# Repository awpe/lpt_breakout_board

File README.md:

lpt_breakout_board
==================

IEEE1284 breakout board

This is a KiCad (http://www.kicad-pcb.org/) project.

Device allows to select controller for I/O pins.

contact information:

fb:    https://www.facebook.com/awpe00
vk:    http://vk.com/id2616793
tw:    http://twitter.com/lantcant
gmail: awpe00@gmail.com

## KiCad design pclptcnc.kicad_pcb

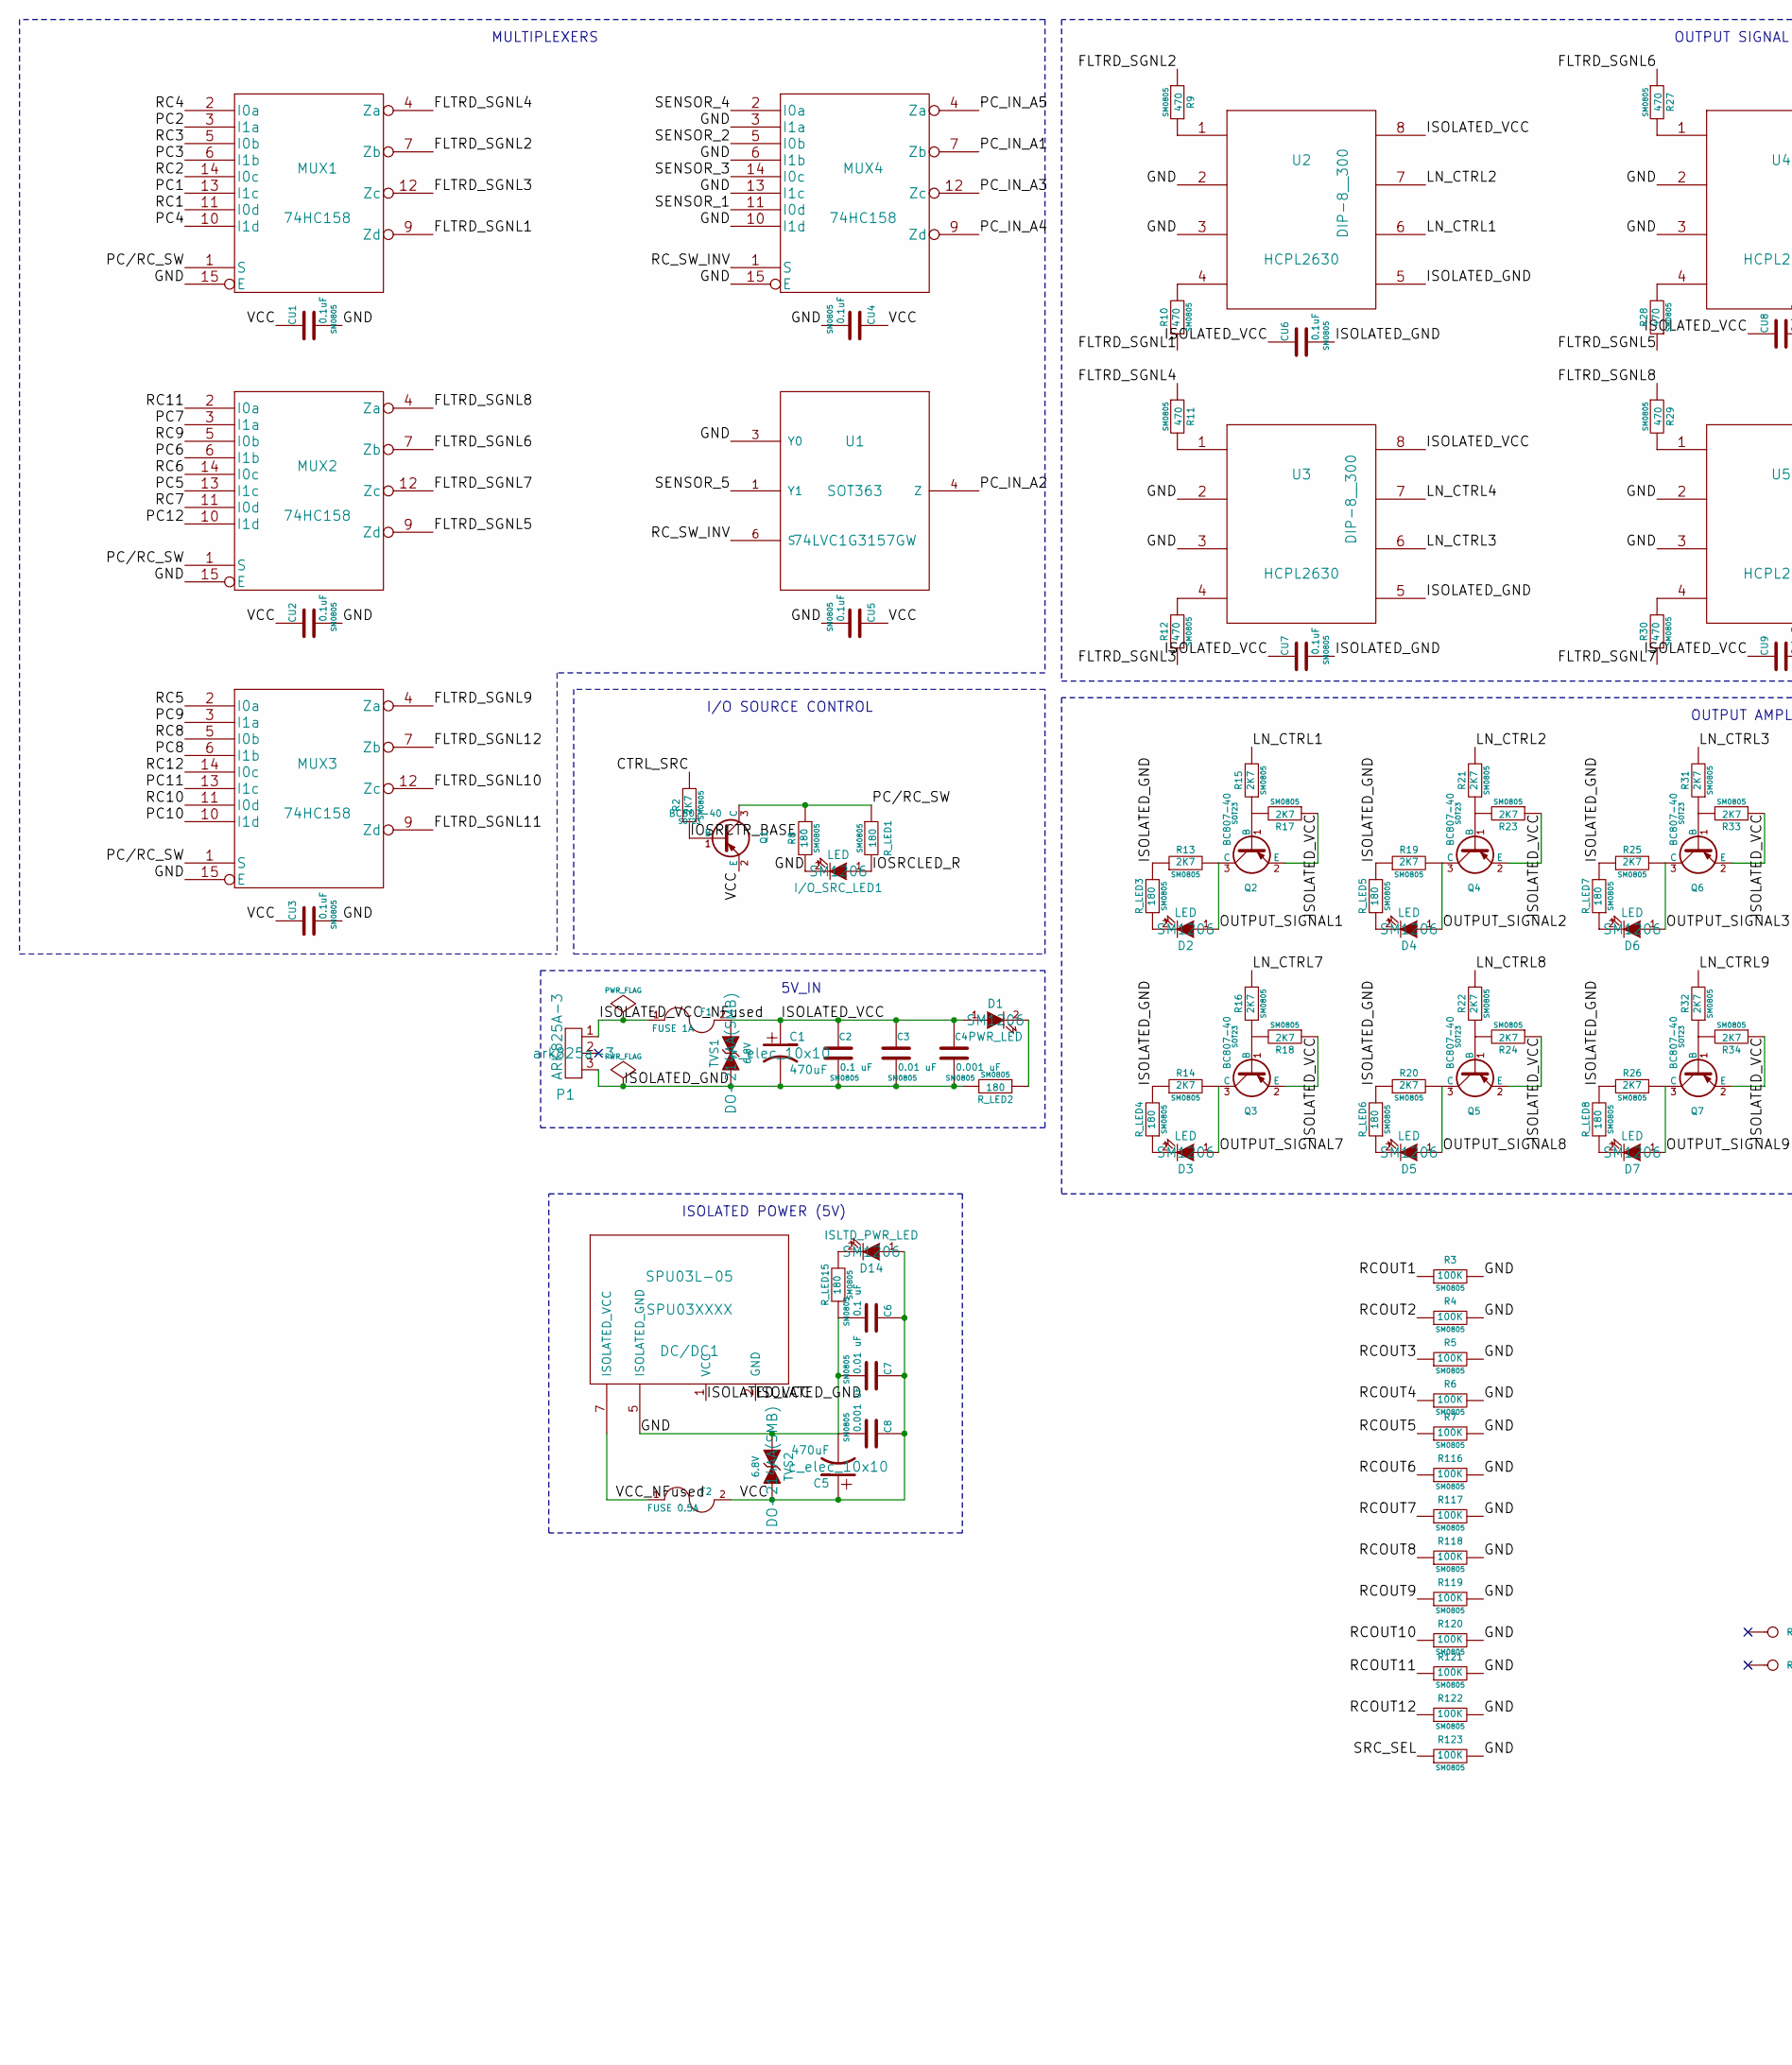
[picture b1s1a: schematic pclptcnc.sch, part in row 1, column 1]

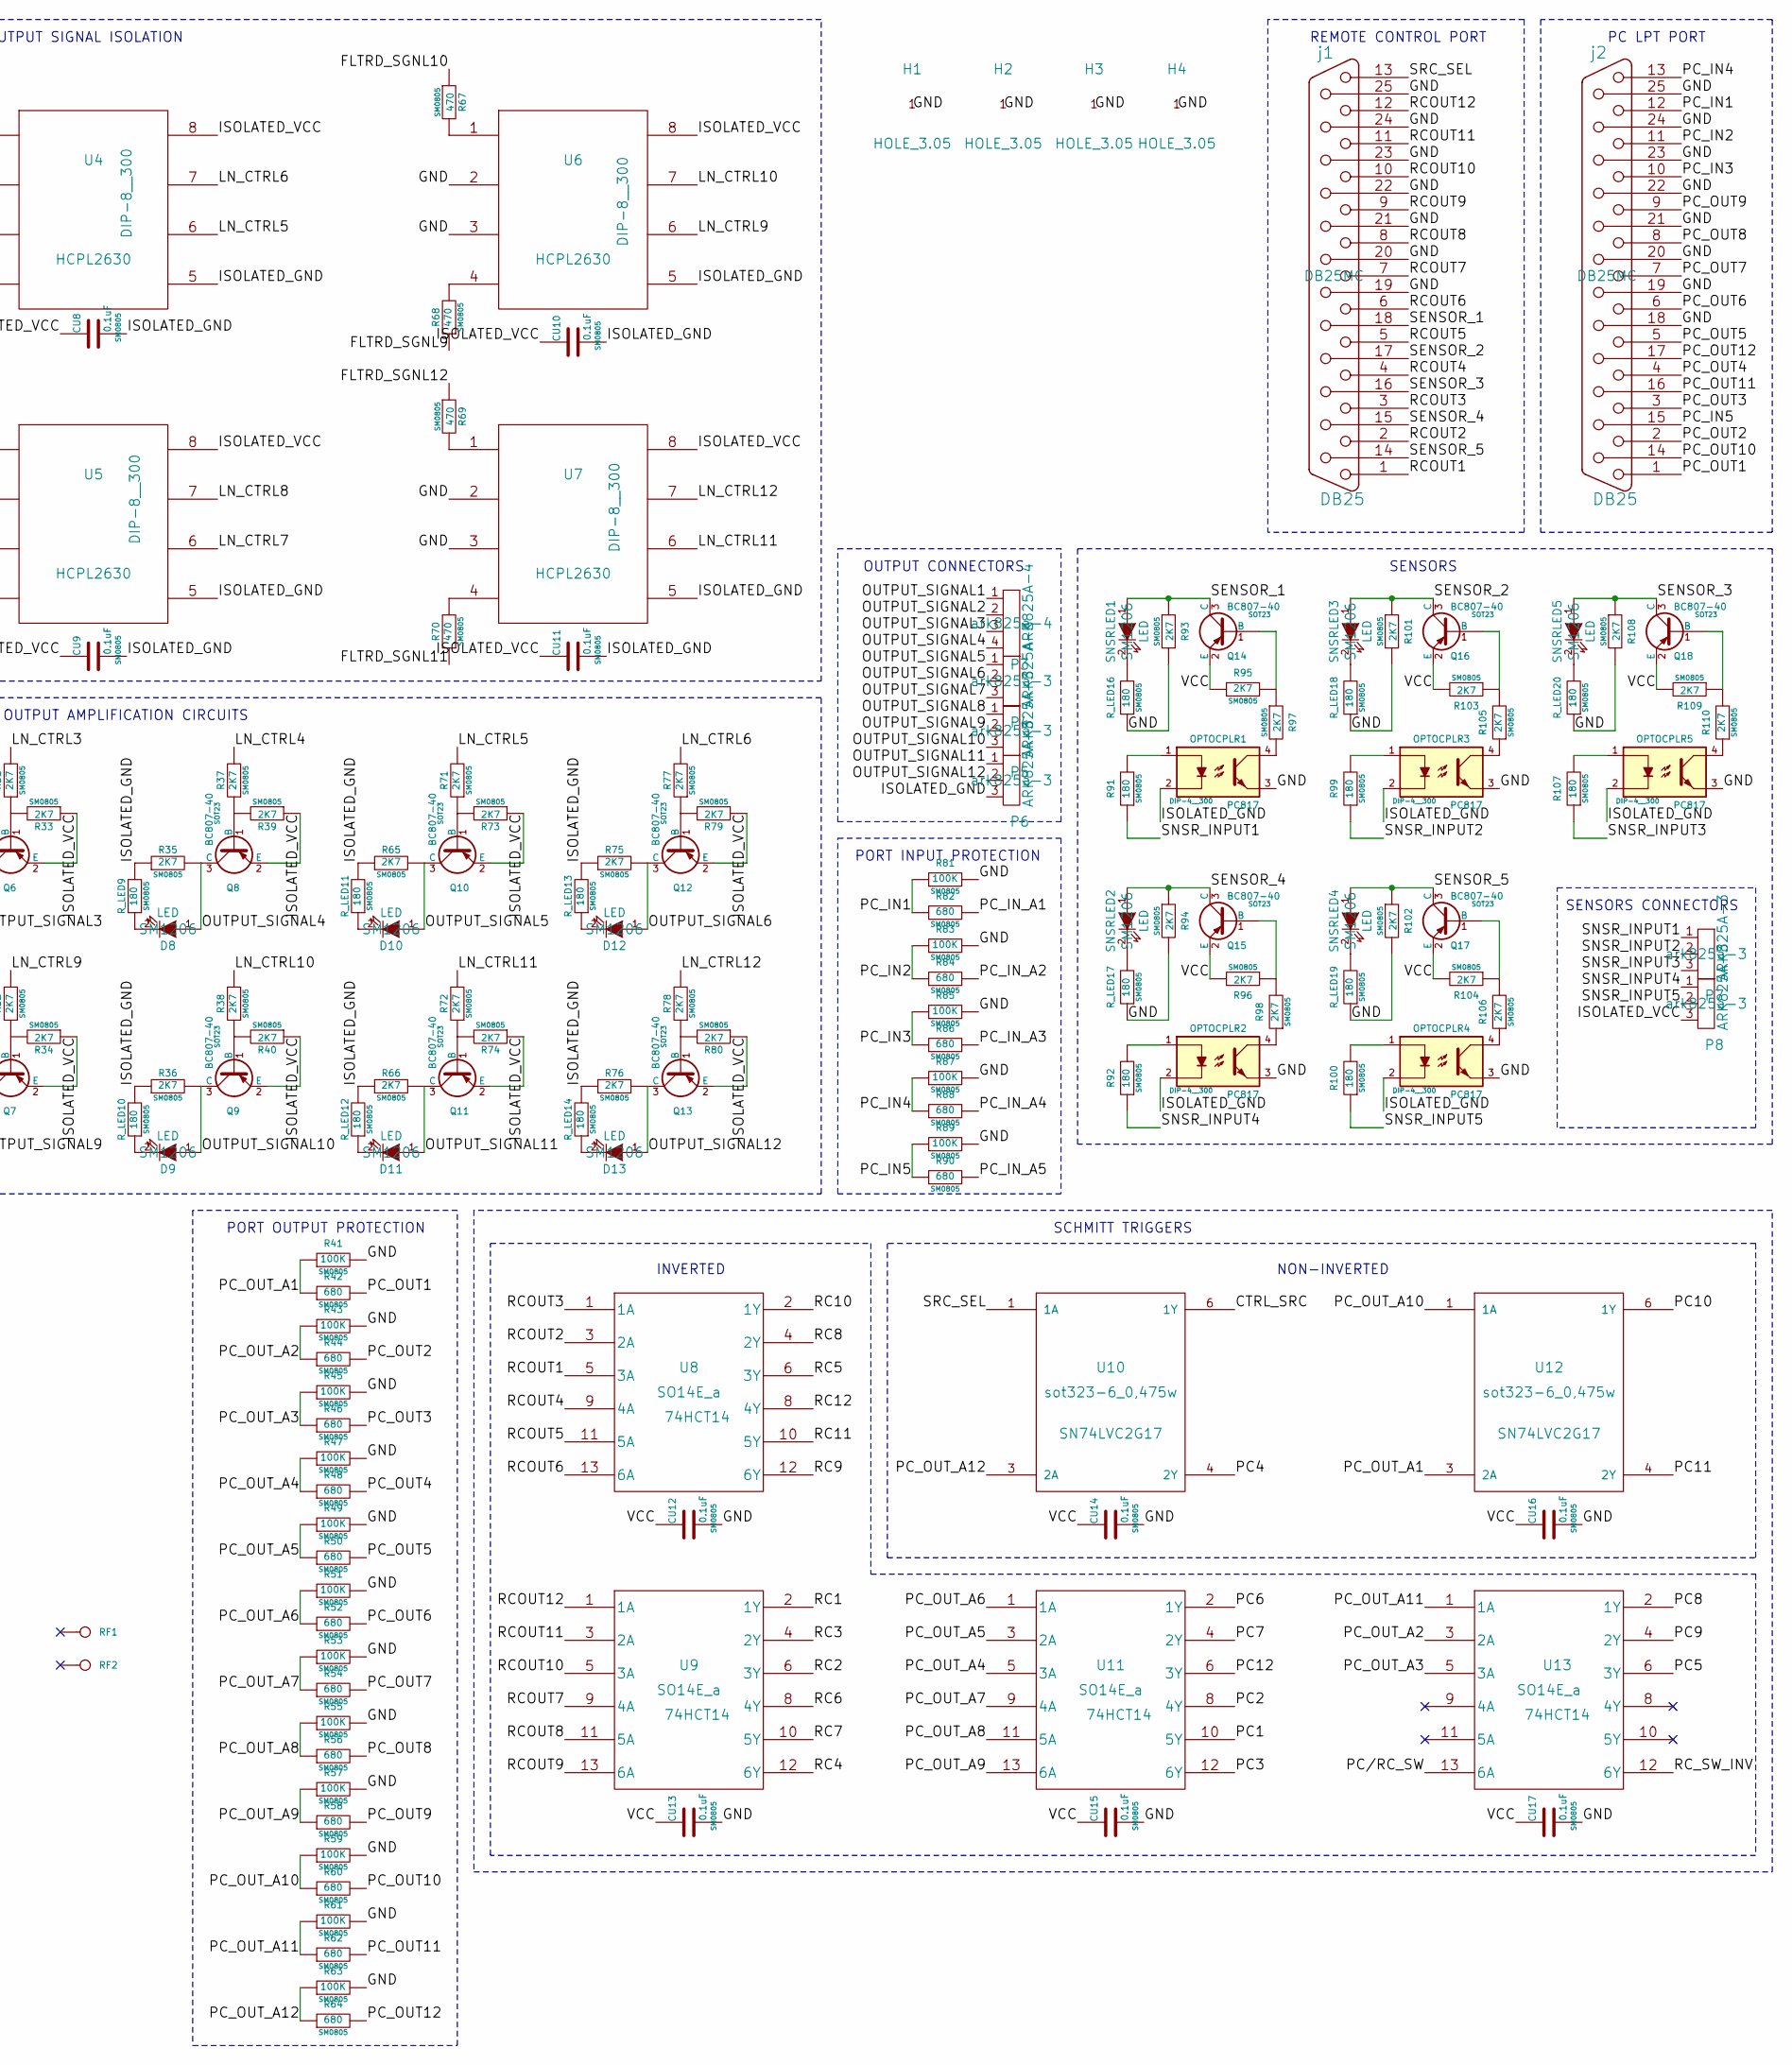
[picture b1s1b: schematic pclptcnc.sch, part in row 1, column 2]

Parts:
C1, C5: 470uF; c_elec_10x10
C2, C6: 0.1 uF; SM0805
C3, C7: 0.01 uF; SM0805
C4, C8: 0.001 uF; SM0805
CU1, CU2, CU3, CU4, CU5, CU6, CU7, CU8, CU9, CU10, CU11, CU12, CU13, CU14, CU15, CU16, CU17: 0.1uF; SM0805
D1: PWR_LED; SM1206
D2, D3, D4, D5, D6, D7, D8, D9, D10, D11, D12, D13: LED; SM1206
D14: ISLTD_PWR_LED; SM1206
DC/DC1: SPU03L-05; SPU03XXXX
F1: FUSE 1A
F2: FUSE 0.5A
H1, H2, H3, H4: HOLE_3.05
I/O_SRC_LED1: LED; SM1206
MUX1, MUX2, MUX3, MUX4: 74HC158
OPTOCPLR1, OPTOCPLR2, OPTOCPLR3, OPTOCPLR4, OPTOCPLR5: PC817; DIP-4__300
P1, P4, P5, P6, P7, P8: ARK825A-3; ark825a-3
P3: ARK825A-4; ark825a-4
Q1, Q2, Q3, Q4, Q5, Q6, Q7, Q8, Q9, Q10, Q11, Q12, Q13, Q14, Q15, Q16, Q17, Q18: BC807-40; SOT23
R2, R13, R14, R15, R16, R17, R18, R19, R20, R21, R22, R23, R24, R25, R26, R31, R32, R33, R34, R35, R36, R37, R38, R39, R40, R65, R66, R71, R72, R73, R74, R75, R76, R77, R78, R79, R80, R93, R94, R95, R96, R97, R98, R101, R102, R103, R104, R105, R106, R108, R109, R110: 2K7; SM0805
R3, R4, R5, R6, R7, R41, R43, R45, R47, R49, R51, R53, R55, R57, R59, R61, R63, R81, R83, R85, R87, R89, R116, R117, R118, R119, R120, R121, R122, R123: 100K; SM0805
R8, R91, R92, R99, R100, R107: 180; SM0805
R9, R10, R11, R12, R27, R28, R29, R30, R67, R68, R69, R70: 470; SM0805
R42, R44, R46, R48, R50, R52, R54, R56, R58, R60, R62, R64, R82, R84, R86, R88, R90: 680; SM0805
RF1, RF2: CONN_1
R_LED1, R_LED2, R_LED3, R_LED4, R_LED5, R_LED6, R_LED7, R_LED8, R_LED9, R_LED10, R_LED11, R_LED12, R_LED13, R_LED14, R_LED15, R_LED16, R_LED17, R_LED18, R_LED19, R_LED20: 180; SM0805
SNSRLED1, SNSRLED2, SNSRLED3, SNSRLED4, SNSRLED5: LED; SM1206
TVS1, TVS2: 6.8V; DO-214AA(SMB)
U1: 74LVC1G3157GW; SOT363
U2, U3, U4, U5, U6, U7: HCPL2630; DIP-8__300
U8, U9, U11, U13: 74HCT14; SO14E_a
U10, U12: SN74LVC2G17; sot323-6_0,475w
j1, j2: DB25; DB25MC

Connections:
/CTRL_SRC: R2.1, U10.6 (1Y)
/FLTRD_SGNL1: MUX1.9 (Zd), R10.1
/FLTRD_SGNL2: MUX1.7 (Zb), R9.1
/FLTRD_SGNL3: MUX1.12 (Zc), R12.1
/FLTRD_SGNL4: MUX1.4 (Za), R11.1
/FLTRD_SGNL5: MUX2.9 (Zd), R28.1
/FLTRD_SGNL6: MUX2.7 (Zb), R27.1
/FLTRD_SGNL7: MUX2.12 (Zc), R30.1
/FLTRD_SGNL8: MUX2.4 (Za), R29.1
/FLTRD_SGNL9: MUX3.4 (Za), R68.1
/FLTRD_SGNL10: MUX3.12 (Zc), R67.1
/FLTRD_SGNL11: MUX3.9 (Zd), R70.1
/FLTRD_SGNL12: MUX3.7 (Zb), R69.1
/IOSRCLED_R: I/O_SRC_LED1.1 (A), R_LED1.2
/IOSRCTR_BASE: Q1.1 (B), R2.2
/ISOLATED_GND: C1.2, C2.2, C3.2, C4.2, CU6.2, CU7.2, CU8.2, CU9.2, CU10.2, CU11.2, DC/DC1.2 (GND), OPTOCPLR1.2, OPTOCPLR2.2, OPTOCPLR3.2, OPTOCPLR4.2, OPTOCPLR5.2, P1.3, P6.3, R13.1, R14.1, R19.1, R20.1, R25.1, R26.1, R35.1, R36.1, R65.1, R66.1, R75.1, R76.1, R_LED2.2, R_LED3.2, R_LED4.2, R_LED5.2, R_LED6.2, R_LED7.2, R_LED8.2, R_LED9.2, R_LED10.2, R_LED11.2, R_LED12.2, R_LED13.2, R_LED14.2, TVS1.1 (A), U2.5 (GND), U3.5 (GND), U4.5 (GND), U5.5 (GND), U6.5 (GND), U7.5 (GND)
/ISOLATED_VCC: C1.1, C2.1, C3.1, C4.1, CU6.1, CU7.1, CU8.1, CU9.1, CU10.1, CU11.1, D1.1 (A), DC/DC1.1 (VCC), F1.2, P8.3, Q2.2 (E), Q3.2 (E), Q4.2 (E), Q5.2 (E), Q6.2 (E), Q7.2 (E), Q8.2 (E), Q9.2 (E), Q10.2 (E), Q11.2 (E), Q12.2 (E), Q13.2 (E), R17.1, R18.1, R23.1, R24.1, R33.1, R34.1, R39.1, R40.1, R73.1, R74.1, R79.1, R80.1, TVS1.2 (K), U2.8 (VCC), U3.8 (VCC), U4.8 (VCC), U5.8 (VCC), U6.8 (VCC), U7.8 (VCC)
/ISOLATED_VCC_NFused: F1.1, P1.1
/LN_CTRL1: R15.2, U2.6 (V2)
/LN_CTRL2: R21.2, U2.7 (V1)
/LN_CTRL3: R31.2, U3.6 (V2)
/LN_CTRL4: R37.2, U3.7 (V1)
/LN_CTRL5: R71.2, U4.6 (V2)
/LN_CTRL6: R77.2, U4.7 (V1)
/LN_CTRL7: R16.2, U5.6 (V2)
/LN_CTRL8: R22.2, U5.7 (V1)
/LN_CTRL9: R32.2, U6.6 (V2)
/LN_CTRL10: R38.2, U6.7 (V1)
/LN_CTRL11: R72.2, U7.6 (V2)
/LN_CTRL12: R78.2, U7.7 (V1)
/OUTPUT_SIGNAL1: D2.1 (A), P3.1, Q2.3 (C), R13.2
/OUTPUT_SIGNAL2: D4.1 (A), P3.2, Q4.3 (C), R19.2
/OUTPUT_SIGNAL3: D6.1 (A), P3.3, Q6.3 (C), R25.2
/OUTPUT_SIGNAL4: D8.1 (A), P3.4, Q8.3 (C), R35.2
/OUTPUT_SIGNAL5: D10.1 (A), P4.1, Q10.3 (C), R65.2
/OUTPUT_SIGNAL6: D12.1 (A), P4.2, Q12.3 (C), R75.2
/OUTPUT_SIGNAL7: D3.1 (A), P4.3, Q3.3 (C), R14.2
/OUTPUT_SIGNAL8: D5.1 (A), P5.1, Q5.3 (C), R20.2
/OUTPUT_SIGNAL9: D7.1 (A), P5.2, Q7.3 (C), R26.2
/OUTPUT_SIGNAL10: D9.1 (A), P5.3, Q9.3 (C), R36.2
/OUTPUT_SIGNAL11: D11.1 (A), P6.1, Q11.3 (C), R66.2
/OUTPUT_SIGNAL12: D13.1 (A), P6.2, Q13.3 (C), R76.2
/PC1: MUX1.13 (I1c), U11.10 (5Y)
/PC2: MUX1.3 (I1a), U11.8 (4Y)
/PC3: MUX1.6 (I1b), U11.12 (6Y)
/PC4: MUX1.10 (I1d), U10.4 (2Y)
/PC5: MUX2.13 (I1c), U13.6 (3Y)
/PC6: MUX2.6 (I1b), U11.2 (1Y)
/PC7: MUX2.3 (I1a), U11.4 (2Y)
/PC8: MUX3.6 (I1b), U13.2 (1Y)
/PC9: MUX3.3 (I1a), U13.4 (2Y)
/PC10: MUX3.10 (I1d), U12.6 (1Y)
/PC11: MUX3.13 (I1c), U12.4 (2Y)
/PC12: MUX2.10 (I1d), U11.6 (3Y)
/PC/RC_SW: MUX1.1 (S), MUX2.1 (S), MUX3.1 (S), Q1.3 (C), R8.1, R_LED1.1, U13.13 (6A)
/PC_IN1: R81.1, R82.1, j2.12
/PC_IN2: R83.1, R84.1, j2.11
/PC_IN3: R85.1, R86.1, j2.10
/PC_IN4: R87.1, R88.1, j2.13
/PC_IN5: R89.1, R90.1, j2.15
/PC_IN_A1: MUX4.7 (Zb), R82.2
/PC_IN_A2: R84.2, U1.4 (Z)
/PC_IN_A3: MUX4.12 (Zc), R86.2
/PC_IN_A4: MUX4.9 (Zd), R88.2
/PC_IN_A5: MUX4.4 (Za), R90.2
/PC_OUT1: R42.2, j2.1
/PC_OUT2: R44.2, j2.2
/PC_OUT3: R46.2, j2.3
/PC_OUT4: R48.2, j2.4
/PC_OUT5: R50.2, j2.5
/PC_OUT6: R52.2, j2.6
/PC_OUT7: R54.2, j2.7
/PC_OUT8: R56.2, j2.8
/PC_OUT9: R58.2, j2.9
/PC_OUT10: R60.2, j2.14
/PC_OUT11: R62.2, j2.16
/PC_OUT12: R64.2, j2.17
/PC_OUT_A1: R41.1, R42.1, U12.3 (2A)
/PC_OUT_A2: R43.1, R44.1, U13.3 (2A)
/PC_OUT_A3: R45.1, R46.1, U13.5 (3A)
/PC_OUT_A4: R47.1, R48.1, U11.5 (3A)
/PC_OUT_A5: R49.1, R50.1, U11.3 (2A)
/PC_OUT_A6: R51.1, R52.1, U11.1 (1A)
/PC_OUT_A7: R53.1, R54.1, U11.9 (4A)
/PC_OUT_A8: R55.1, R56.1, U11.11 (5A)
/PC_OUT_A9: R57.1, R58.1, U11.13 (6A)
/PC_OUT_A10: R59.1, R60.1, U12.1 (1A)
/PC_OUT_A11: R61.1, R62.1, U13.1 (1A)
/PC_OUT_A12: R63.1, R64.1, U10.3 (2A)
/RC1: MUX1.11 (I0d), U9.2 (1Y)
/RC2: MUX1.14 (I0c), U9.6 (3Y)
/RC3: MUX1.5 (I0b), U9.4 (2Y)
/RC4: MUX1.2 (I0a), U9.12 (6Y)
/RC5: MUX3.2 (I0a), U8.6 (3Y)
/RC6: MUX2.14 (I0c), U9.8 (4Y)
/RC7: MUX2.11 (I0d), U9.10 (5Y)
/RC8: MUX3.5 (I0b), U8.4 (2Y)
/RC9: MUX2.5 (I0b), U8.12 (6Y)
/RC10: MUX3.11 (I0d), U8.2 (1Y)
/RC11: MUX2.2 (I0a), U8.10 (5Y)
/RC12: MUX3.14 (I0c), U8.8 (4Y)
/RCOUT1: R3.1, U8.5 (3A), j1.1
/RCOUT2: R4.1, U8.3 (2A), j1.2
/RCOUT3: R5.1, U8.1 (1A), j1.3
/RCOUT4: R6.1, U8.9 (4A), j1.4
/RCOUT5: R7.1, U8.11 (5A), j1.5
/RCOUT6: R116.1, U8.13 (6A), j1.6
/RCOUT7: R117.1, U9.9 (4A), j1.7
/RCOUT8: R118.1, U9.11 (5A), j1.8
/RCOUT9: R119.1, U9.13 (6A), j1.9
/RCOUT10: R120.1, U9.5 (3A), j1.10
/RCOUT11: R121.1, U9.3 (2A), j1.11
/RCOUT12: R122.1, U9.1 (1A), j1.12
/RC_SW_INV: MUX4.1 (S), U1.6 (S), U13.12 (6Y)
/SENSOR_1: MUX4.11 (I0d), Q14.3 (C), R93.1, SNSRLED1.1 (A), j1.18
/SENSOR_2: MUX4.5 (I0b), Q16.3 (C), R101.1, SNSRLED3.1 (A), j1.17
/SENSOR_3: MUX4.14 (I0c), Q18.3 (C), R108.1, SNSRLED5.1 (A), j1.16
/SENSOR_4: MUX4.2 (I0a), Q15.3 (C), R94.1, SNSRLED2.1 (A), j1.15
/SENSOR_5: Q17.3 (C), R102.1, SNSRLED4.1 (A), U1.1 (Y1), j1.14
/SNSR_INPUT1: P7.1, R91.1
/SNSR_INPUT2: P7.2, R99.1
/SNSR_INPUT3: P7.3, R107.1
/SNSR_INPUT4: P8.1, R92.1
/SNSR_INPUT5: P8.2, R100.1
/SRC_SEL: R123.1, U10.1 (1A), j1.13
/VCC_NFused: DC/DC1.7 (ISOLATED_VCC), F2.1
GND: C5.2, C6.2, C7.2, C8.2, CU1.2, CU2.2, CU3.2, CU4.2, CU5.2, CU12.2, CU13.2, CU14.2, CU15.2, CU16.2, CU17.2, DC/DC1.5 (ISOLATED_GND), H1.1, H2.1, H3.1, H4.1, I/O_SRC_LED1.2 (K), MUX1.8 (GND), MUX1.15 (E), MUX2.8 (GND), MUX2.15 (E), MUX3.8 (GND), MUX3.15 (E), MUX4.3 (I1a), MUX4.6 (I1b), MUX4.8 (GND), MUX4.10 (I1d), MUX4.13 (I1c), MUX4.15 (E), OPTOCPLR1.3, OPTOCPLR2.3, OPTOCPLR3.3, OPTOCPLR4.3, OPTOCPLR5.3, R3.2, R4.2, R5.2, R6.2, R7.2, R8.2, R41.2, R43.2, R45.2, R47.2, R49.2, R51.2, R53.2, R55.2, R57.2, R59.2, R61.2, R63.2, R81.2, R83.2, R85.2, R87.2, R89.2, R93.2, R94.2, R101.2, R102.2, R108.2, R116.2, R117.2, R118.2, R119.2, R120.2, R121.2, R122.2, R123.2, R_LED15.1, R_LED16.1, R_LED17.1, R_LED18.1, R_LED19.1, R_LED20.1, TVS2.1 (A), U1.2 (GND), U1.3 (Y0), U2.2 (C1), U2.3 (C2), U3.2 (C1), U3.3 (C2), U4.2 (C1), U4.3 (C2), U5.2 (C1), U5.3 (C2), U6.2 (C1), U6.3 (C2), U7.2 (C1), U7.3 (C2), U8.7 (GND), U9.7 (GND), U10.2 (GND), U11.7 (GND), U12.2 (GND), U13.7 (GND), j1.19, j1.20, j1.21, j1.22, j1.23, j1.24, j1.25, j2.18, j2.19, j2.20, j2.21, j2.22, j2.23, j2.24, j2.25
unnamed: D12.2 (K), R_LED13.1
unnamed: Q3.1 (B), R16.1, R18.2
unnamed: Q12.1 (B), R77.1, R79.2
unnamed: D5.2 (K), R_LED6.1
unnamed: Q5.1 (B), R22.1, R24.2
unnamed: D3.2 (K), R_LED4.1
unnamed: Q6.1 (B), R31.1, R33.2
unnamed: Q8.1 (B), R37.1, R39.2
unnamed: D8.2 (K), R_LED9.1
unnamed: D6.2 (K), R_LED7.1
unnamed: Q10.1 (B), R71.1, R73.2
unnamed: D10.2 (K), R_LED11.1
unnamed: D13.2 (K), R_LED14.1
unnamed: Q13.1 (B), R78.1, R80.2
unnamed: Q11.1 (B), R72.1, R74.2
unnamed: D11.2 (K), R_LED12.1
unnamed: Q7.1 (B), R32.1, R34.2
unnamed: D7.2 (K), R_LED8.1
unnamed: Q9.1 (B), R38.1, R40.2
unnamed: D9.2 (K), R_LED10.1
unnamed: OPTOCPLR3.1, R99.2
unnamed: Q15.1 (B), R96.1, R98.2
unnamed: OPTOCPLR2.1, R92.2
unnamed: Q16.1 (B), R103.1, R105.2
unnamed: OPTOCPLR4.1, R100.2
unnamed: Q17.1 (B), R104.1, R106.2
unnamed: D1.2 (K), R_LED2.1
unnamed: OPTOCPLR1.4, R97.2
unnamed: OPTOCPLR5.1, R107.2
unnamed: Q18.1 (B), R109.1, R110.2
unnamed: OPTOCPLR1.1, R91.2
unnamed: Q14.1 (B), R95.2, R97.1
unnamed: R10.2, U2.4 (A2)
unnamed: R9.2, U2.1 (A1)
unnamed: D14.2 (K), R_LED15.2
unnamed: Q2.1 (B), R15.1, R17.2
unnamed: R_LED16.2, SNSRLED1.2 (K)
unnamed: D2.2 (K), R_LED3.1
unnamed: R28.2, U4.4 (A2)
unnamed: R27.2, U4.1 (A1)
unnamed: R12.2, U3.4 (A2)
unnamed: R11.2, U3.1 (A1)
unnamed: R30.2, U5.4 (A2)
unnamed: R29.2, U5.1 (A1)
unnamed: R70.2, U7.4 (A2)
unnamed: Q4.1 (B), R21.1, R23.2
unnamed: D4.2 (K), R_LED5.1
unnamed: R67.2, U6.1 (A1)
unnamed: R68.2, U6.4 (A2)
unnamed: R69.2, U7.1 (A1)
unnamed: OPTOCPLR3.4, R105.1
unnamed: OPTOCPLR5.4, R110.1
unnamed: R_LED20.2, SNSRLED5.2 (K)
unnamed: R_LED18.2, SNSRLED3.2 (K)
unnamed: R_LED17.2, SNSRLED2.2 (K)
unnamed: OPTOCPLR2.4, R98.1
unnamed: R_LED19.2, SNSRLED4.2 (K)
unnamed: OPTOCPLR4.4, R106.1
VCC: C5.1, C6.1, C7.1, C8.1, CU1.1, CU2.1, CU3.1, CU4.1, CU5.1, CU12.1, CU13.1, CU14.1, CU15.1, CU16.1, CU17.1, D14.1 (A), F2.2, MUX1.16 (VCC), MUX2.16 (VCC), MUX3.16 (VCC), MUX4.16 (VCC), Q1.2 (E), Q14.2 (E), Q15.2 (E), Q16.2 (E), Q17.2 (E), Q18.2 (E), R95.1, R96.2, R103.2, R104.2, R109.2, TVS2.2 (K), U1.5 (VCC), U8.14 (VCC), U9.14 (VCC), U10.5 (VCC), U11.14 (VCC), U12.5 (VCC), U13.14 (VCC)

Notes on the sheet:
5V_IN
REMOTE CONTROL PORT
PC LPT PORT
SCHMITT TRIGGERS
INVERTED
NON-INVERTED
ISOLATED POWER (5V)
SENSORS CONNECTORS
SENSORS
MULTIPLEXERS
I/O SOURCE CONTROL
OUTPUT SIGNAL ISOLATION
OUTPUT AMPLIFICATION CIRCUITS
OUTPUT CONNECTORS
PORT INPUT PROTECTION
PORT OUTPUT PROTECTION

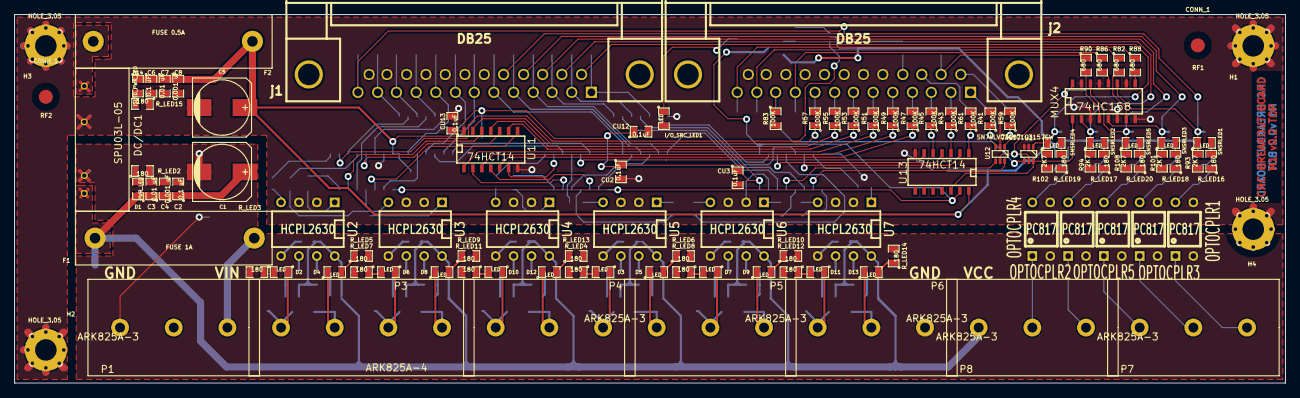
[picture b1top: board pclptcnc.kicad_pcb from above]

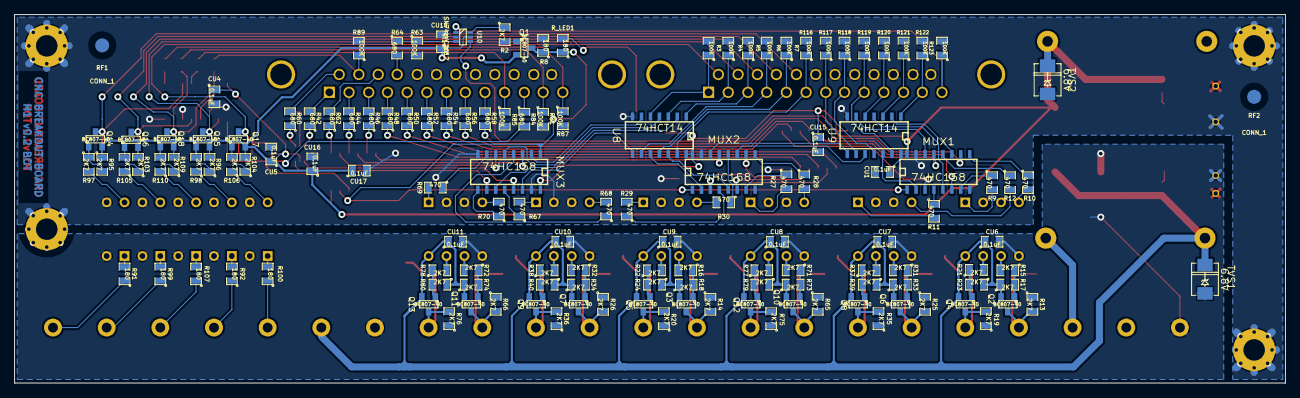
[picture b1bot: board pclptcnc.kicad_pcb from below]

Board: 2 copper layers, 180.5 x 52.3 mm, 244 parts (138 on the bottom side), 186 nets.

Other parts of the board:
RF1#2, RF2#2: CONN_1; RF

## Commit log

2013-11-01 second commit
2013-11-01 working on
2013-11-01 rking on pcb design only
2013-11-01 regular
2013-11-02 merged all libraries
2013-11-02 futher library development
2013-11-05 05.11.1305.11.1305.11.1305.11.1305.11.13
2013-11-06 huge optocouplers movement
2013-11-06 близкая компоновка
2013-11-06 version 0.2a completed
2013-11-07 revised first PCB version
2013-11-07 odd komponents removed
2013-11-07 odd files removed
2013-11-07 components list added
2013-11-07 revision b
2013-11-07 zofproject added
2013-11-07 ignore add
2013-11-07 gitignore and .directory deleted
2014-05-25 starting work on adding emergency stop switch selection
